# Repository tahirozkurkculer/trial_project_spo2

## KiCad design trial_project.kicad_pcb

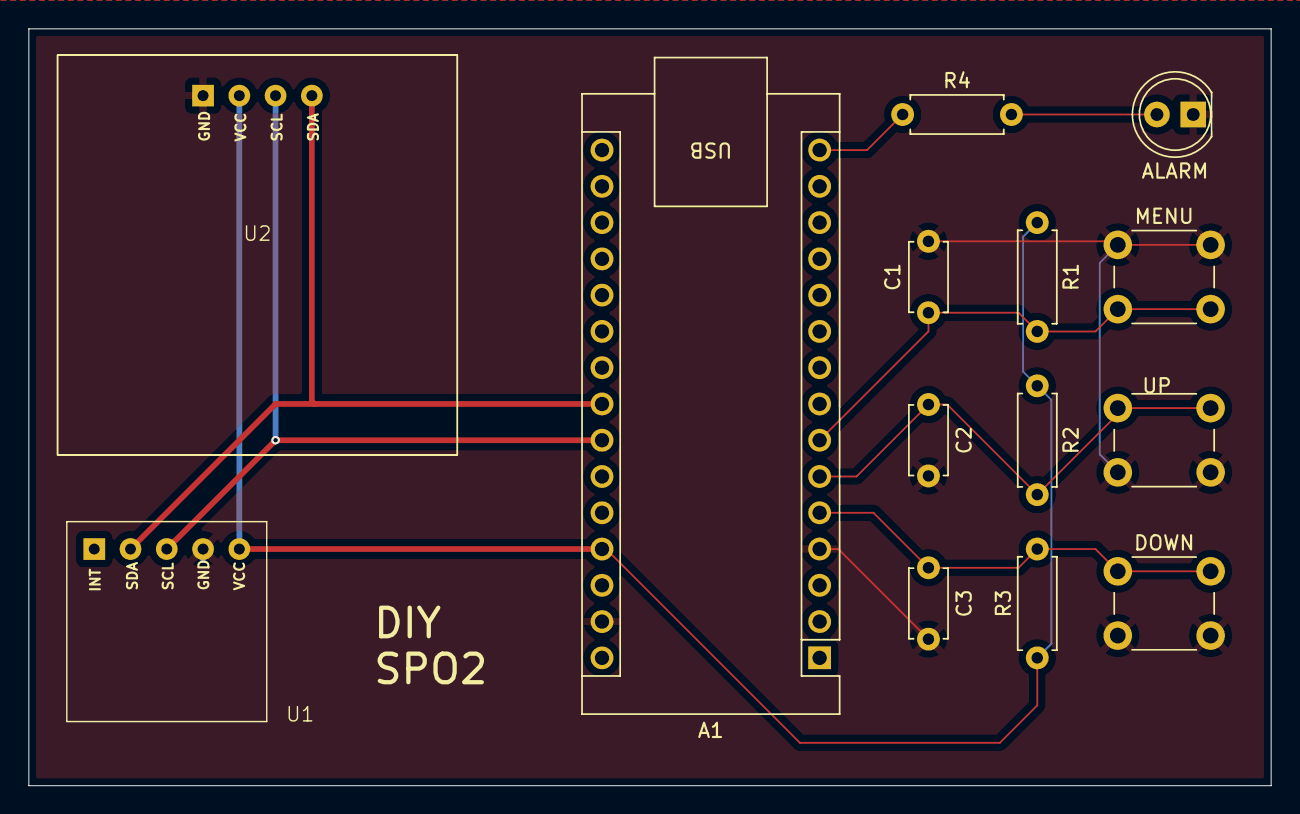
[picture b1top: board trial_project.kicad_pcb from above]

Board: 2 copper layers, 87.0 x 53.0 mm, 14 parts (0 on the bottom side), 9 nets.

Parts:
A1: Arduino_Nano_v3.x; Arduino_Nano
ALARM: LED; LED_D5.0mm
C1, C2, C3: 100n; C_Disc_D4.7mm_W2.5mm_P5.00mm
DOWN: SW_Push; SW_PUSH_6mm
MENU: SW_Push; SW_PUSH_6mm
R1, R2, R3, R4: 1K; R_Axial_DIN0207_L6.3mm_D2.5mm_P7.62mm_Horizontal
U1: MAX30102; MAX30102_Module
U2: SSD1306
UP: SW_Push; SW_PUSH_6mm

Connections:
+5V: A1.27 (+5V), R1.1, R2.1, R3.1, U1.5 (VCC), U2.2 (VCC)
GND: A1.4 (GND), A1.29 (GND), ALARM.1 (K), C1.2, C2.2, C3.2, DOWN.1, MENU.1, U1.4 (GND), U2.1 (GND), UP.1
unnamed: A1.23 (A4), U1.2 (SDA), U2.4 (SDA)
unnamed: A1.24 (A5), U1.3 (SCL), U2.3 (SCL)
unnamed: A1.5 (D2), C3.1, DOWN.2, R3.2
unnamed: A1.6 (D3), C2.1, R2.2, UP.2
unnamed: A1.7 (D4), C1.1, MENU.2, R1.2
unnamed: A1.15 (D12), R4.1
unnamed: ALARM.2 (A), R4.2

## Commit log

2026-06-23 ssd1306 place changed
2026-06-24 PCB design is ongoing
    an issue with track between VCC and GND
2026-06-25 completed version of project
